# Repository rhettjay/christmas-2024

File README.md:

# Christmas Tree 2024

The below image demonstrates the correct orientation and placement of the diodes and resistors.
Follow the diagram on the back of the pcb. With the shorter leg (cathode) going into the square hole from the front of the pcb and the long leg (anode) going into the round hole.
After the led is soldered in place you can safely snip the legs.

solder the battery clip by adding solder to both of the square pads on either side of the large circle such that it will fit in the following orientation:

Install 220 Ohm resistors at R1, R2, and R3. Each LED has its own series resistor, so the LEDs do not share a current-limiting resistor. The value is a starting point for typical red LEDs on 3.3 V; check the LED datasheet before using a different color or part. Do not bypass the resistors.

The on position of the switch is in the position marked on the board. Make sure to solder the switch with the three legs fitting into the solder pads.

## External 3.3 V power

J1 is an unpopulated two-pin through-hole header. Pin 1 (square pad, marked `-`) is the return; pin 2 (marked `+`) accepts 3.3 V. The existing switch still controls the LEDs.

JP1 is on the back of the PCB and selects the power source. Its factory copper bridge joins pads 1 and 2 for battery power. To use J1 while leaving the battery installed, cut the bridge between pads 1 and 2, check that the pads are no longer connected, then solder a bridge between pads 2 and 3. Bridge only one side of JP1 at a time. To return to battery power, remove the 2–3 bridge and reconnect pads 1 and 2.

The files in `gerber/` describe the original battery-only board. Regenerate fabrication files from the KiCad project to manufacture the board with J1 and JP1.

Alternatively you can just enjoy the ornament for what it is without any leds.

Merry Christmas!

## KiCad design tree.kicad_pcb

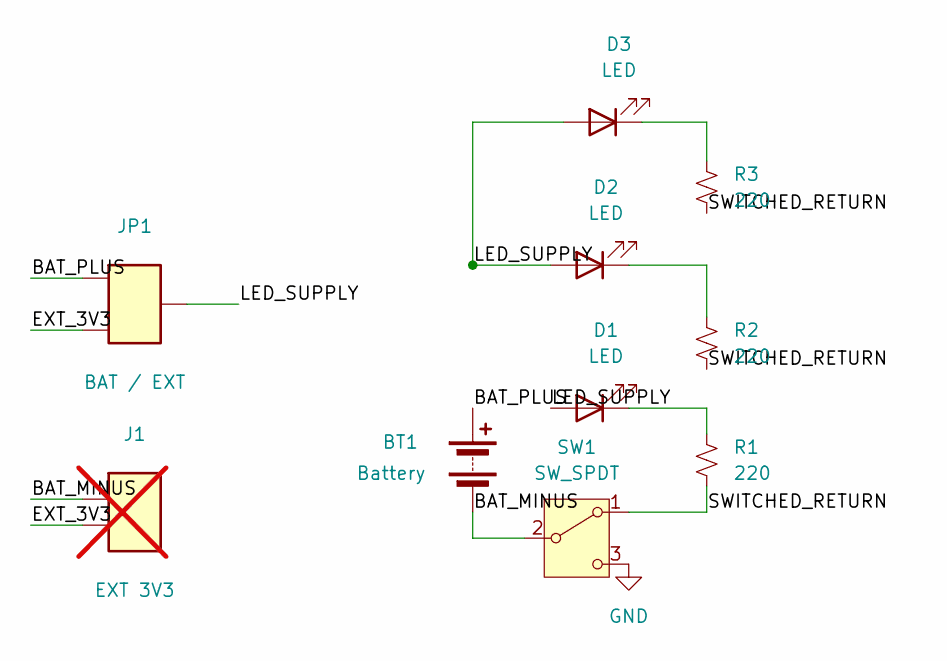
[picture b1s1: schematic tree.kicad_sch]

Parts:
BT1: Battery; BatteryHolder_Multicomp_BC-2001_1x2032
D1, D2, D3: LED; LED_D1.8mm_W3.3mm_H2.4mm
J1: EXT 3V3; PinHeader_1x02_P2.54mm_Vertical; not fitted
JP1: BAT / EXT; SolderJumper-3_P1.3mm_Bridged12_Pad1.0x1.5mm
R1, R2, R3: 220; R_0805_2012Metric_Pad1.20x1.40mm_HandSolder
SW1: SW_SPDT; SW_SPDT_PCM12C03

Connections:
BAT_MINUS: BT1.2 (-), J1.1 (-), SW1.2 (B)
BAT_PLUS: BT1.1 (+), JP1.1 (BAT)
EXT_3V3: J1.2 (+3V3), JP1.3 (EXT)
GND: SW1.3 (C)
LED_SUPPLY: D1.2 (A), D2.2 (A), D3.2 (A), JP1.2 (OUT)
unnamed: D1.1 (K), R1.1
unnamed: D2.1 (K), R2.1
unnamed: D3.1 (K), R3.1
SWITCHED_RETURN: R1.2, R2.2, R3.2, SW1.1 (A)

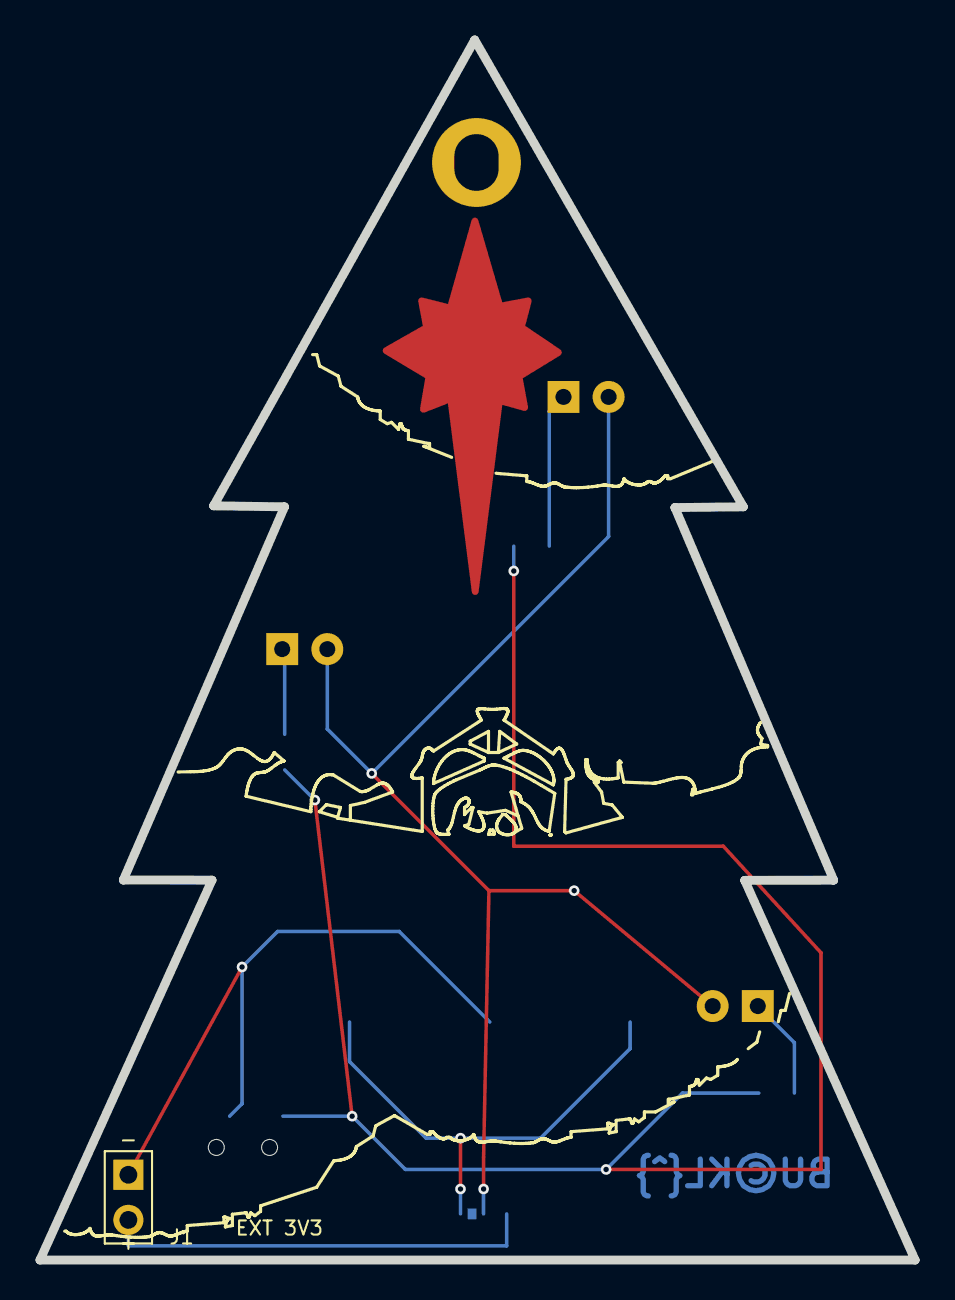
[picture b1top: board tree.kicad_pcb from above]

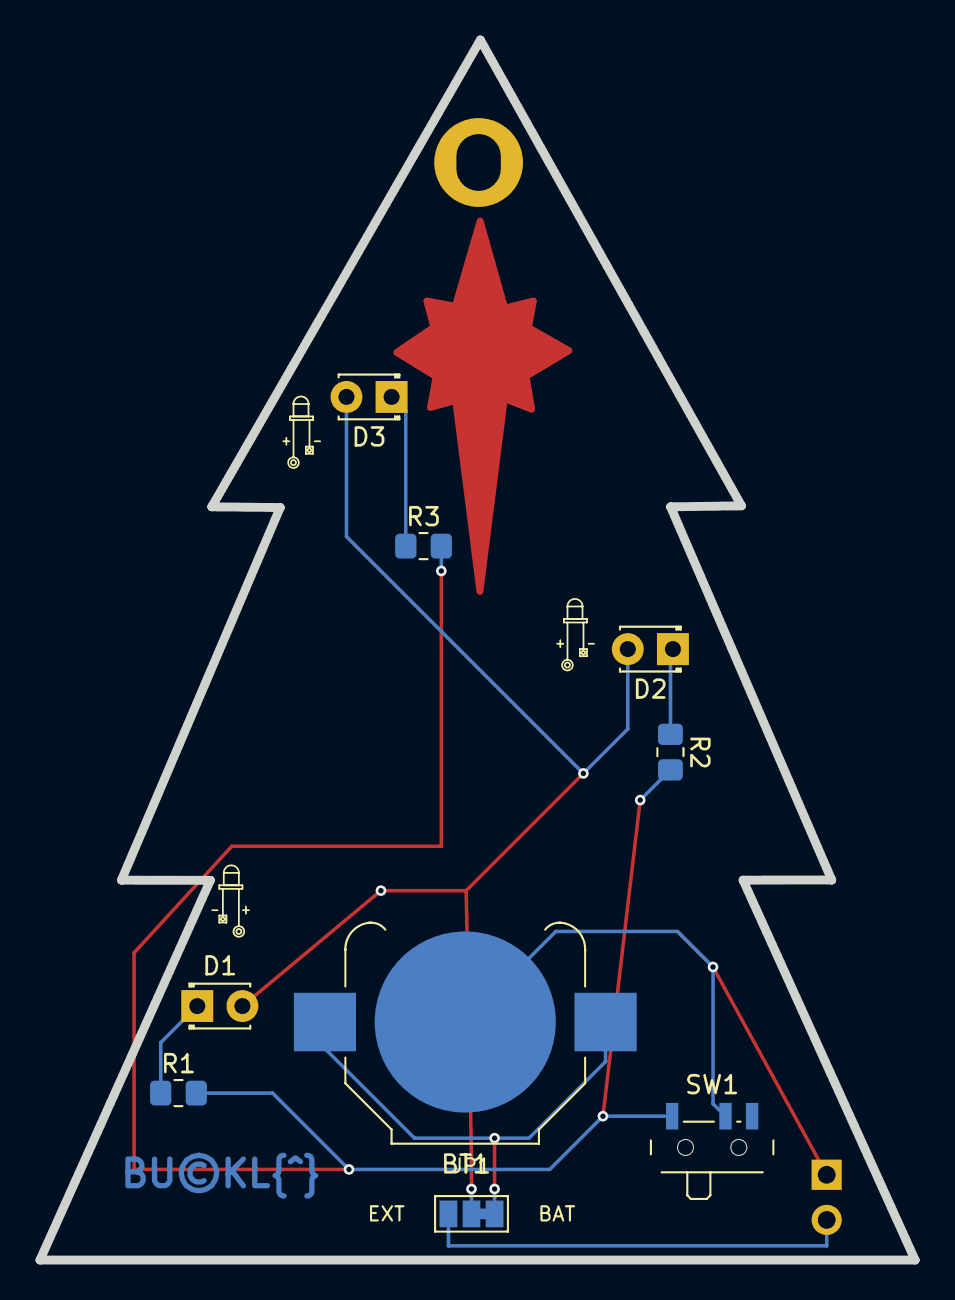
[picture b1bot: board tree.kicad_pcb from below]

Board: 2 copper layers, 49.3 x 68.7 mm, 10 parts (9 on the bottom side), 8 nets.

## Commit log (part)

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2024-12-17 pcb files
2024-12-17 tree images
2024-12-17 Merry Christmas
2024-12-19 battery image
2024-12-19 battery
